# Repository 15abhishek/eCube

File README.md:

# eCube

New repo, will update this when its done.

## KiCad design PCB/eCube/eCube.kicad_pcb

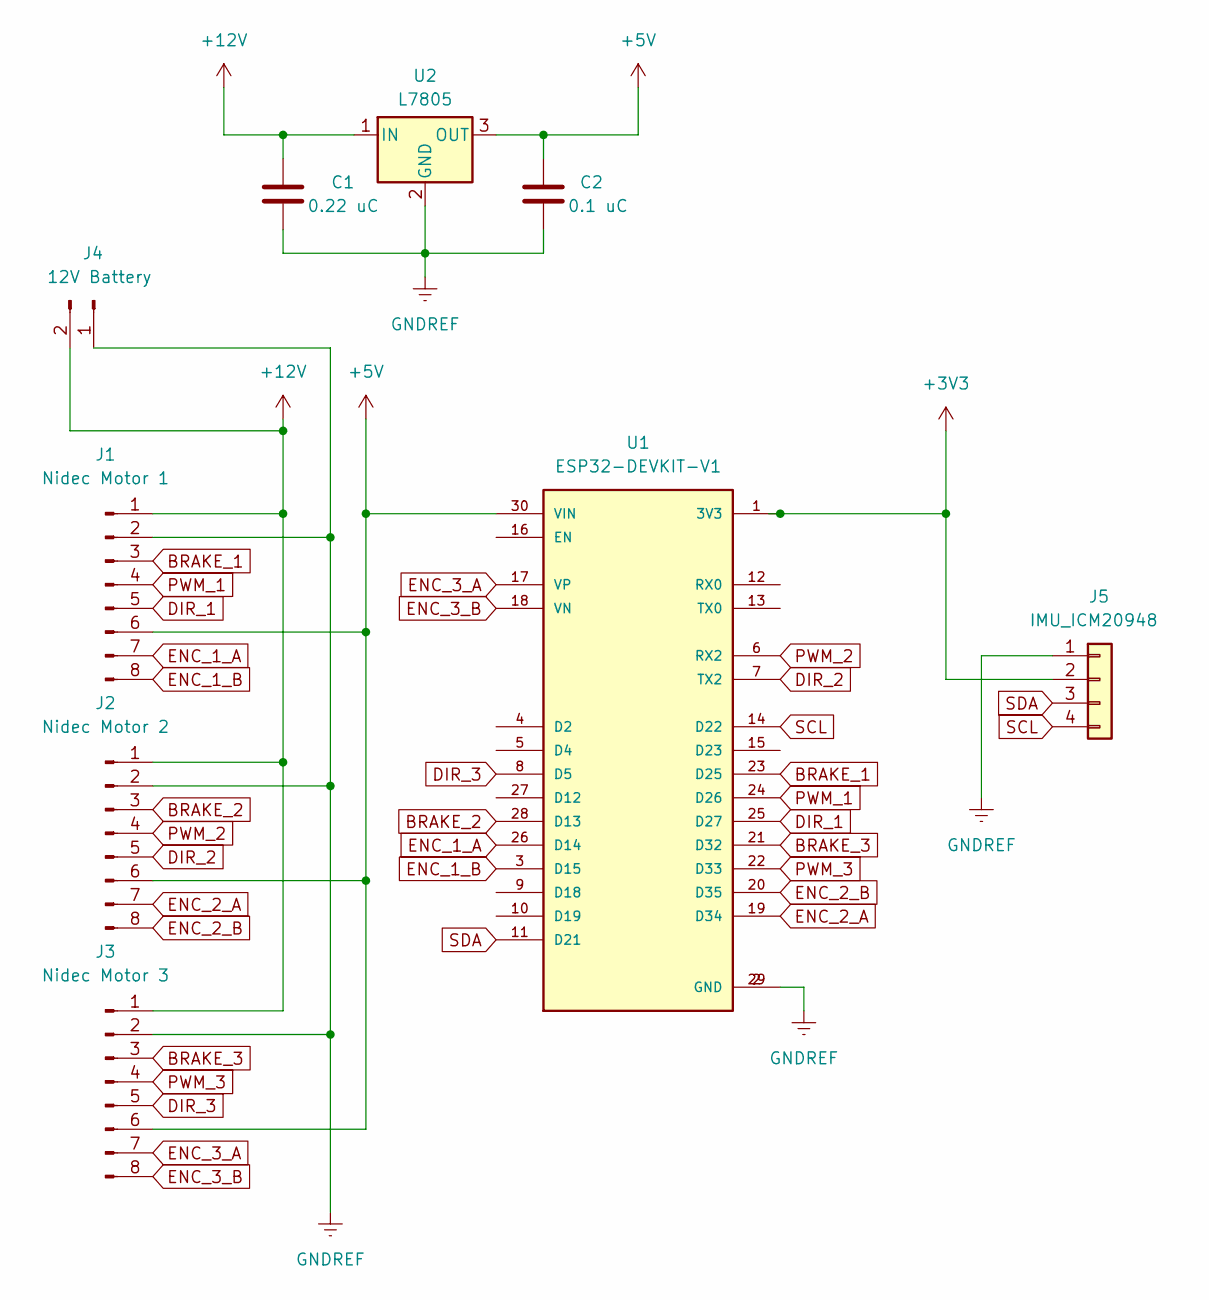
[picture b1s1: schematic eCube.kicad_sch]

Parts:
C1: 0.22 uC; CP_Radial_D10.0mm_P2.50mm
C2: 0.1 uC; CP_Radial_D10.0mm_P2.50mm
J1: Nidec Motor 1; Molex_KK-254_AE-6410-08A_1x08_P2.54mm_Vertical
J2: Nidec Motor 2; Molex_KK-254_AE-6410-08A_1x08_P2.54mm_Vertical
J3: Nidec Motor 3; Molex_KK-254_AE-6410-08A_1x08_P2.54mm_Vertical
J4: 12V Battery; AMASS_XT60-M_1x02_P7.20mm_Vertical
J5: IMU_ICM20948; Molex_KK-254_AE-6410-04A_1x04_P2.54mm_Vertical
U1: ESP32-DEVKIT-V1; MODULE_ESP32_DEVKIT_V1; PARTREV N/A
U2: L7805; PinHeader_1x03_P2.54mm_Vertical

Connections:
+3V3: J5.2, U1.1 (3V3)
+5V: C2.1, J1.6, J2.6, J3.6, U1.30 (VIN), U2.3 (OUT)
+12V: C1.1, J1.1, J2.1, J3.1, J4.2, U2.1 (IN)
BRAKE_1: J1.3, U1.23 (D25)
BRAKE_2: J2.3, U1.28 (D13)
BRAKE_3: J3.3, U1.21 (D32)
DIR_1: J1.5, U1.25 (D27)
DIR_2: J2.5, U1.7 (TX2)
DIR_3: J3.5, U1.8 (D5)
ENC_1_A: J1.7, U1.26 (D14)
ENC_1_B: J1.8, U1.3 (D15)
ENC_2_A: J2.7, U1.19 (D34)
ENC_2_B: J2.8, U1.20 (D35)
ENC_3_A: J3.7, U1.17 (VP)
ENC_3_B: J3.8, U1.18 (VN)
GNDREF: C1.2, C2.2, J1.2, J2.2, J3.2, J4.1, J5.1, U1.2 (GND), U1.29 (GND), U2.2 (GND)
PWM_1: J1.4, U1.24 (D26)
PWM_2: J2.4, U1.6 (RX2)
PWM_3: J3.4, U1.22 (D33)
SCL: J5.4, U1.14 (D22)
SDA: J5.3, U1.11 (D21)

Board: 2 copper layers, 9 parts (0 on the bottom side), 21 nets, no tracks yet.

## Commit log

2024-06-12 added files
